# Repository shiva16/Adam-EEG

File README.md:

# Adam-EEG

**India's first open-hardware 32-channel EEG / biopotential acquisition board** — a quad-ADS1299 analog front end driven by a dual-ATmega328 controller, designed in EAGLE by [Soul Scientific](https://github.com/shiva16) in 2015.

Adam-EEG packs four Texas Instruments **ADS1299** 24-bit, 8-channel simultaneous-sampling analog front ends onto one board — 32 truly simultaneous EEG channels, daisy-chained over a single SPI bus — with onboard microSD logging for fully standalone (untethered) recording. It's the original prototype in the Adam-EEG lineage: a from-scratch, low-cost, open alternative to research-grade EEG acquisition hardware.

**Also published at:** [Hackaday.io](https://hackaday.io/project/206308-adam-eeg-open-source-32-channel-eeg-board) · [dev.to](https://dev.to/shiva16/adam-eeg-an-open-source-32-channel-eeg-board-from-2015-quad-ads1299-dual-atmega328-2gfi) · [NeuroTechX/awesome-bci](https://github.com/NeuroTechX/awesome-bci#consumer-and-diy-devices) ([merged](https://github.com/NeuroTechX/awesome-bci/pull/92))

---

## Table of contents

- [Why this exists](#why-this-exists)
- [Technical specifications](#technical-specifications)
- [Connectors & pinout](#connectors--pinout)
- [Passive component reference](#passive-component-reference)
- [System architecture](#system-architecture)
- [Repository contents](#repository-contents)
- [Getting started](#getting-started)
- [Safety & disclaimer](#safety--disclaimer)
- [Roadmap](#roadmap)
- [Contributing](#contributing)
- [License](#license)

---

## Why this exists

Research-grade multichannel EEG hardware is expensive and closed. Adam-EEG set out to prove that a **32-channel, simultaneous-sampling, standalone-logging** EEG acquisition board could be built from commodity parts, in a hobbyist CAD tool, at a fraction of the cost — fully open, so anyone can build on it rather than starting from a datasheet.

## Technical specifications

| Subsystem | Detail |
|---|---|
| **Analog front end** | 4 × Texas Instruments **ADS1299** — 24-bit, 8-channel, simultaneous-sampling, low-noise biopotential ADC |
| **Total channels** | **32** unipolar channels + common reference, fully simultaneous (no muxing) |
| **AFE interconnect** | Multi-device SPI **daisy-chain** — shared `SCLK`/`DIN`/`DOUT`/`DRDY`, individual `CS1`–`CS4` per ADS1299 |
| **Controller** | 2 × **ATmega328** (SMD, Arduino-compatible core) |
| **Programming** | 2 × 6-pin AVR ISP headers |
| **Onboard storage** | microSD socket — standalone data logging, no host PC required |
| **Power** | Onboard bipolar analog rail generation: LM2663 switched-capacitor inverter + LP5907 / TPS723xx LDOs for clean split supplies to the AFEs |
| **Clocking** | 2 × crystal oscillators |
| **I/O** | 6 × 1×2, 3 × 1×8, 1 × 1×11, 1 × 1×18 pin headers (electrode + expansion) |
| **Board** | 2-layer, **97.2 × 81.9 mm** (~79.6 cm²), 2 × Ø3.2 mm mounting holes |
| **Complexity** | 354 schematic parts / 229 placed board elements |
| **CAD format** | EAGLE 6.6.0 XML (`.sch` / `.brd`) — single schematic sheet |
| **License** | Apache License 2.0 |

## Connectors & pinout

Extracted directly from the schematic's named nets — real signal names, not inferred from silkscreen alone.

| Connector | Type | Signals | Role |
|---|---|---|---|
| `ARDUINO_CONN` | 1×11 header | `CS1`–`CS4`, `SCLK`, `DIN`, `DOUT`, `DRDY`, `RST`, `PD`, `STRT` | Full SPI daisy-chain + control breakout — lets an external Arduino-compatible host drive all 4 ADS1299 directly, independent of the onboard ATmega328s |
| `ELECTRODES_P&N` | 1×18 header | 18 electrode nets | Primary differential (P/N) electrode input header |
| `ELECTRODES` / `ELECTRODES1` / `ELECTRODES2` | 3× 1×8 header | Per-channel buffered outputs (`1O1`–`8O1`, `1O2`–`8O2`, `1O3`–`8O3`) | Buffered channel-output test/tap points for 3 of the 4 ADS1299s |
| `POWER_PIN` | 1×2 header | `+5V`, `AGND` | Main board power input, feeding the onboard LDO/charge-pump regulation |
| `JP3`–`JP5` | 1×2 jumpers | `DIN`/`JU1`, `DOUT`/`JU2`, `SCLK`/`JU3` | In-line jumpers on the SPI data/clock lines (break/test-point access) |
| `JP1`–`JP2` | 1×2 jumpers | Internal (unlabeled) nets | Present in the schematic; exact function isn't silkscreen-documented — trace before relying on them |

## Passive component reference

Most-used passive values, pulled from the real `value=` attributes in the schematic (useful for a BOM sanity-check or respin):

| Component class | Dominant value | Count | Likely role |
|---|---|---|---|
| Resistor | 5 kΩ | 60 of 69 | Per-channel bias/lead-off network (matches ADS1299's typical RLD topology) |
| Capacitor | 4.7 nF | 48 of 127 | Per-channel input RC filtering |
| Capacitor | 1 µF | 36 of 127 | Local/bulk decoupling |
| Capacitor | 0.1 µF | 28 of 127 | High-frequency decoupling |
| Capacitor | 10 µF / 100 µF | 7 / 4 | Bulk supply-rail reservoirs |
| Crystal | 32.768 kHz (`Y1` or `Y2`, confirmed in schematic text) | 1 of 2 | Real-time/watchdog clock — the second crystal has no frequency called out in the schematic text, verify before assuming a value |

## System architecture

```mermaid
flowchart LR
    subgraph AFE["Analog Front End"]
        A1["ADS1299 #1<br/>ch 1-8"]
        A2["ADS1299 #2<br/>ch 9-16"]
        A3["ADS1299 #3<br/>ch 17-24"]
        A4["ADS1299 #4<br/>ch 25-32"]
    end
    A1 -- "DOUT daisy" --> A2 -- "DOUT daisy" --> A3 -- "DOUT daisy" --> A4
    MCU["Dual ATmega328<br/>controller"]
    A1 <-- "shared SCLK / DIN / DRDY<br/>individual CS1-CS4" --> MCU
    A2 <-.-> MCU
    A3 <-.-> MCU
    A4 <-.-> MCU
    MCU --> SD["microSD<br/>standalone logging"]
    PWR["LM2663 charge pump<br/>+ LP5907 / TPS723xx LDOs"] --> AFE
    ISP["2x AVR ISP header"] --> MCU
```

Each ADS1299 samples 8 channels simultaneously; the four devices share one SPI bus in TI's standard multi-device daisy-chain topology, so all 32 channels are read out in lockstep with no channel-to-channel skew.

## Repository contents

| Path | Description |
|---|---|
| `EEG_64_1.zip` | Full EAGLE source — `EEG_64.sch` (schematic) + `EEG_64_1.brd` (board layout) |
| `LICENSE` | Apache License 2.0 |
| `CONTRIBUTING.md` | How to propose changes, report issues, or contribute a fabricated/tested revision |
| `CODE_OF_CONDUCT.md` | Community standards for this repository |
| `.github/` | Issue and pull request templates |

## Getting started

1. Install [Autodesk EAGLE](https://www.autodesk.com/products/eagle/overview) (a free tier is sufficient — this board's ≤80 cm², 2-layer, single-sheet design was scoped to fit within EAGLE's classic free-tier limits).
2. Clone this repo and unzip `EEG_64_1.zip`.
3. Open `EEG_64.sch` for the schematic or `EEG_64_1.brd` for the board layout — both are standard EAGLE XML and can also be inspected with `eagle2kicad`-style converters if you prefer KiCad.
4. Gerbers are not checked in — export them from the `.brd` via EAGLE's CAM processor if you're sending this to fab.

## Safety & disclaimer

This is an **open-hardware research/prototyping board**, not a certified medical device. It has not undergone FDA/CE or equivalent regulatory clearance, and no formal patient-isolation or leakage-current certification has been performed on this design. If you build and use this board:

- Do **not** use it for clinical diagnosis or treatment decisions.
- Power it only from isolated, battery-backed supplies — never connect a build to mains-powered equipment while it is attached to a person.
- Treat it as you would any DIY biopotential-acquisition project: informed use, at your own risk.

## Roadmap

This 2015 quad-ADS1299 board is the original Adam-EEG prototype. It remains a solid, low-cost 32-channel reference design for anyone building EEG/BCI acquisition hardware from scratch. Later Adam-EEG iterations explore denser single-chip AFE options; this repository stays focused on the original, fully-verified quad-ADS1299 design.

## Contributing

Issues and pull requests are welcome — see [CONTRIBUTING.md](CONTRIBUTING.md). Whether it's a routing improvement, a KiCad conversion, a BOM/sourcing update, or a build log from your own fab run, please open an issue first so we can track it.

## License

Apache License 2.0 — see [LICENSE](LICENSE). You are free to use, modify, and distribute this design, including commercially, provided attribution is preserved.

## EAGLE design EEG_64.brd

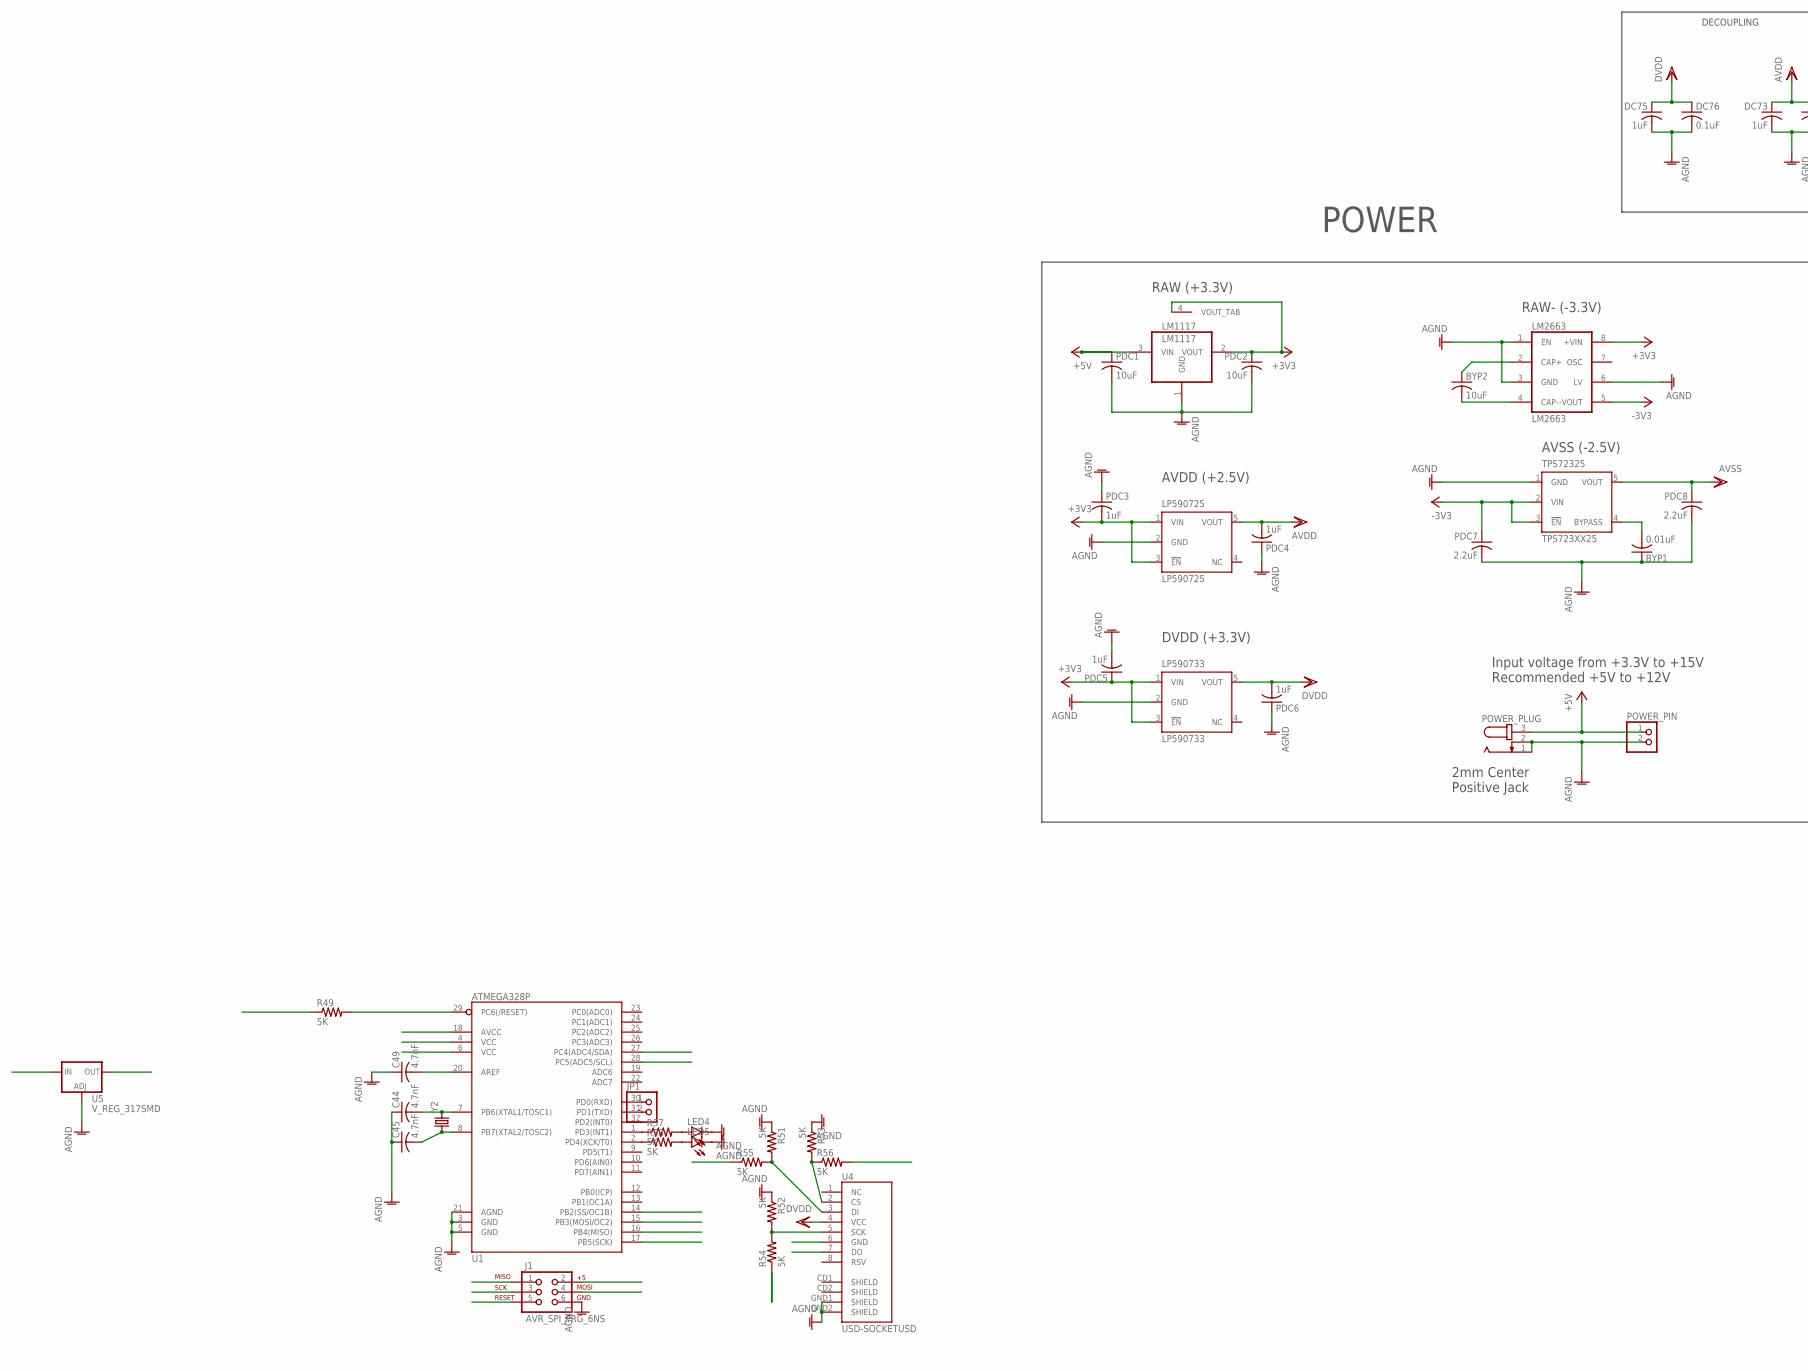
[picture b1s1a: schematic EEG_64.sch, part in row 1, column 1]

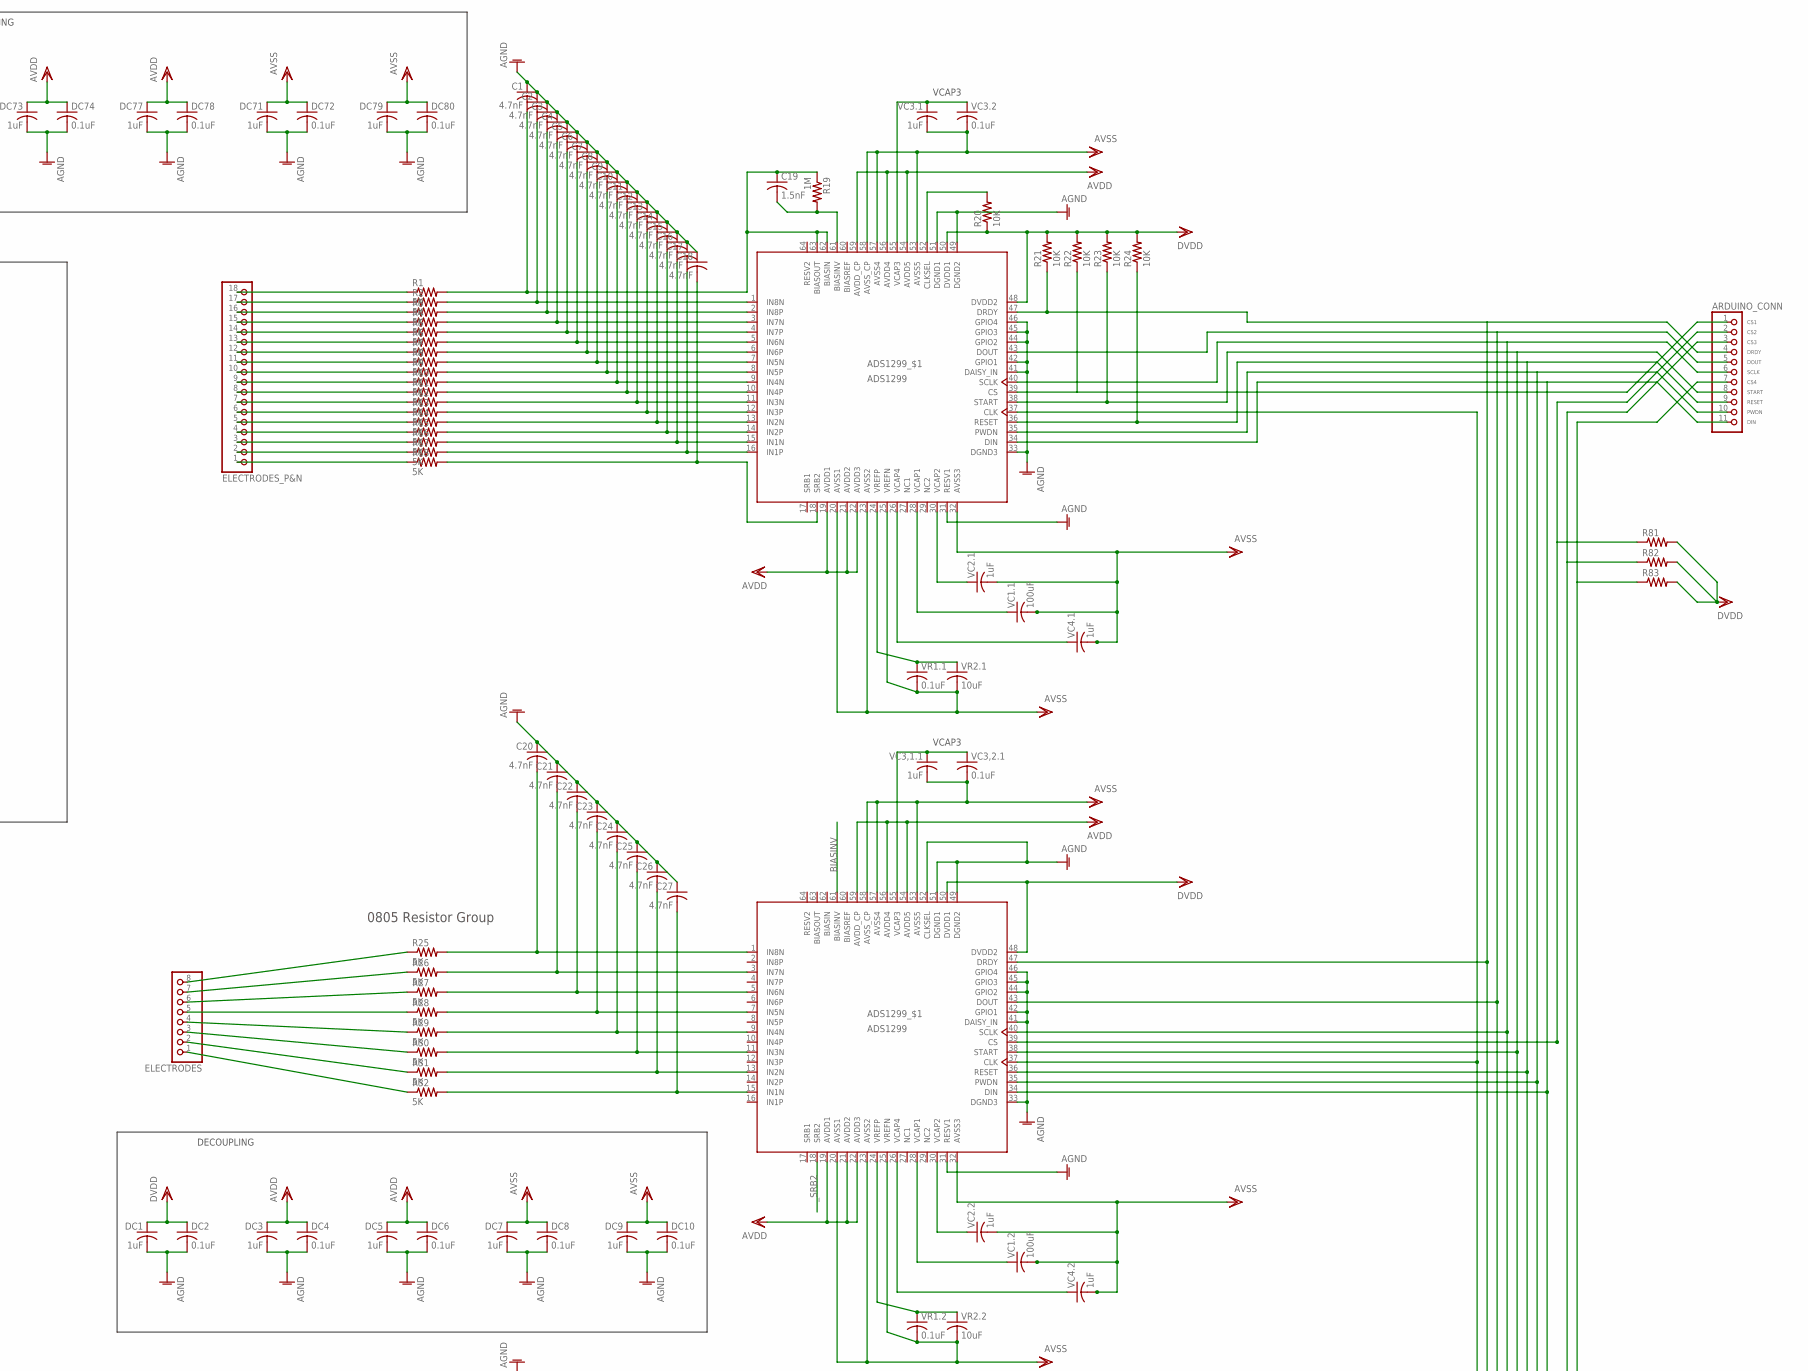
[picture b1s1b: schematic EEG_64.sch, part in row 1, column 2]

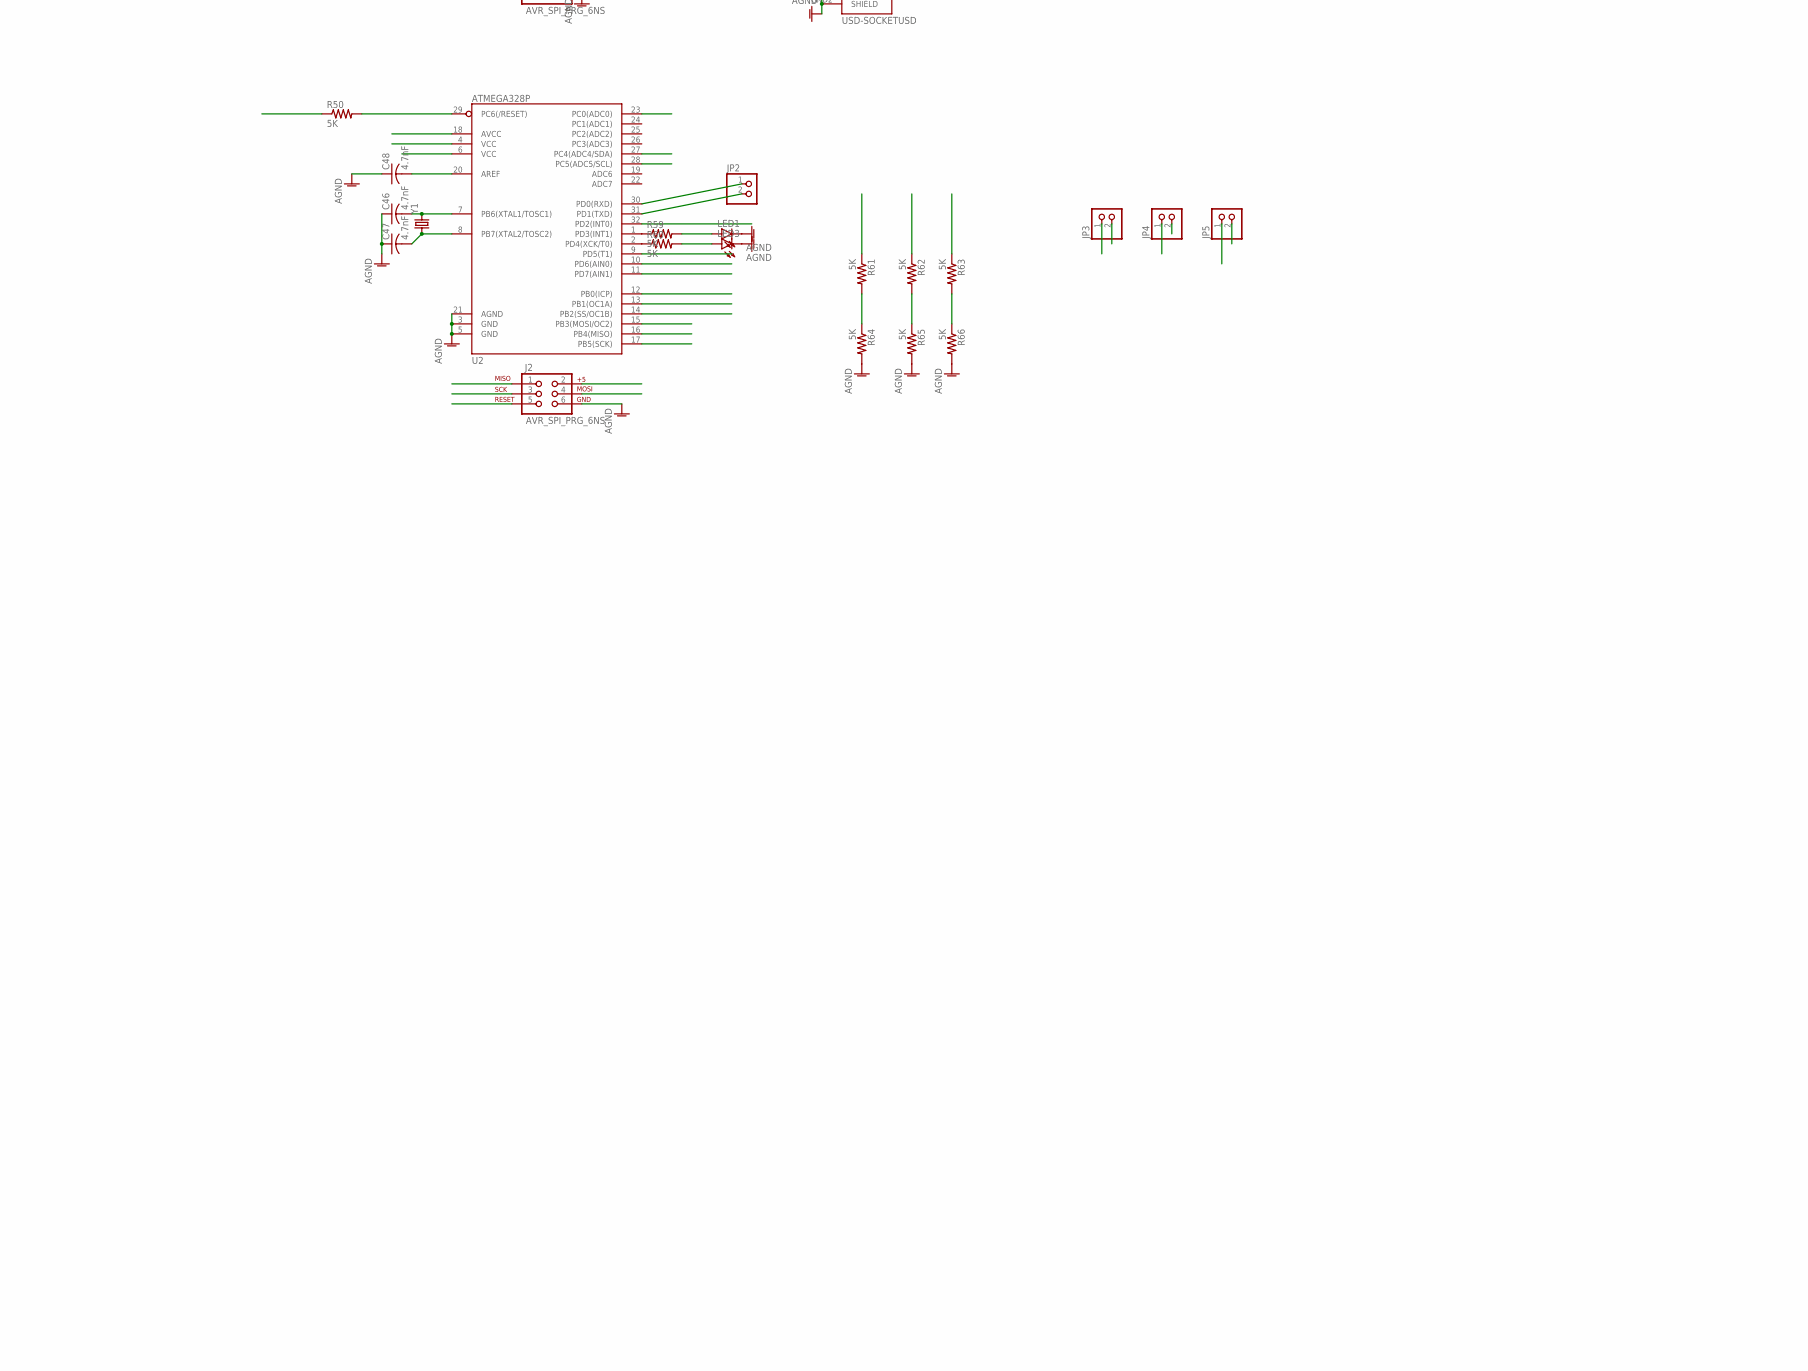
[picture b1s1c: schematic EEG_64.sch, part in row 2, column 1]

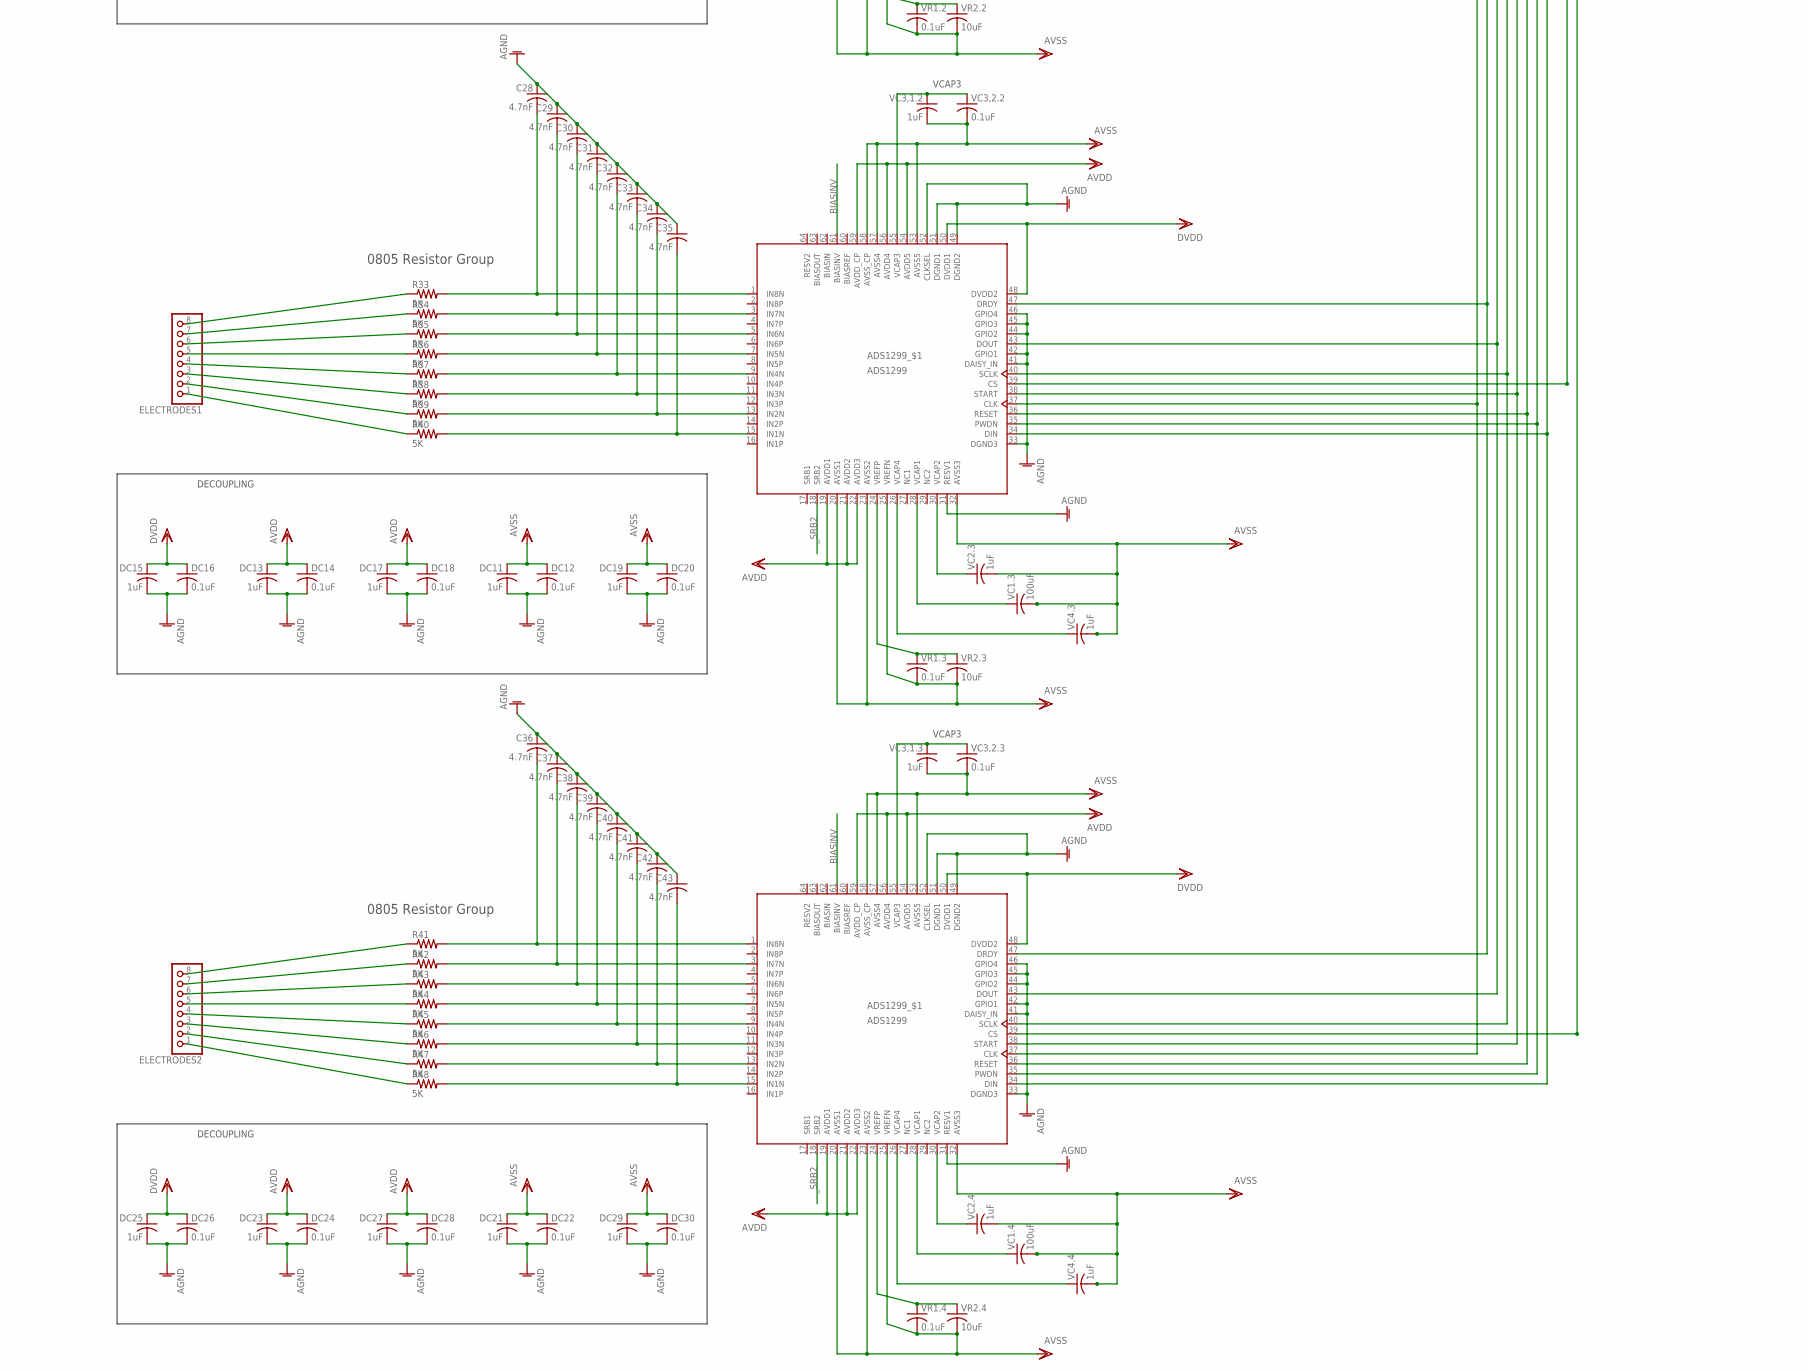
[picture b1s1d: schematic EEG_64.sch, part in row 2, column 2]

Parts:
ADS1, ADS2, ADS3, ADS4: ADS1299; PAG_S-PQFP-G64
ARDUINO_CONN: PINHD-1X11; 1X11
BYP1: 0.01uF; C0603
BYP2: 10uF; C0603
C1, C2, C3, C4, C5, C6, C7, C8, C9, C10, C11, C12, C13, C14, C15, C16, C17, C18, C20, C21, C22, C23, C24, C25, C26, C27, C28, C29, C30, C31, C32, C33, C34, C35, C36, C37, C38, C39, C40, C41, C42, C43, C44, C45, C46, C47, C48, C49: 4.7nF; C0603
C19: 1.5nF; C0603
DC1, DC3, DC5, DC7, DC9, DC11, DC13, DC15, DC17, DC19, DC21, DC23, DC25, DC27, DC29, DC71, DC73, DC75, DC77, DC79: 1uF; C0603
DC2, DC4, DC6, DC8, DC10, DC12, DC14, DC16, DC18, DC20, DC22, DC24, DC26, DC28, DC30, DC72, DC74, DC76, DC78, DC80: 0.1uF; C0603
ELECTRODES, ELECTRODES1, ELECTRODES2: PINHD-1X8; 1X08
ELECTRODES_P&N: PINHD-1X18; 1X18
J1, J2: AVR_SPI_PRG_6NS; 2X3-NS
JP1, JP2, JP3, JP4, JP5: PINHD-1X2; 1X02
LED1, LED3, LED4, LED5: LED0603; LED-0603
LM1117: LM1117; SOT223
LM2663: LM2663; SO-08
LP590725: LP590725; SOT23-DBV
LP590733: LP590733; SOT23-DBV
PDC1, PDC2: 10uF; C0603
PDC3, PDC4, PDC5, PDC6: 1uF; C0603
PDC7, PDC8: 2.2uF; C0603
POWER_PIN: PINHD-1X2; 1X02
POWER_PLUG: JACK-PLUG0; SPC4077
R1, R2, R3, R4, R5, R6, R7, R8, R9, R10, R11, R12, R13, R14, R15, R16, R17, R18, R25, R26, R27, R28, R29, R30, R31, R32, R33, R34, R35, R36, R37, R38, R39, R40, R41, R42, R43, R44, R45, R46, R47, R48, R49, R50, R51, R52, R53, R54, R55, R56, R57, R58, R59, R60, R61, R62, R63, R64, R65, R66: 5K; R0603
R19: 1M; R0603
R20, R21, R22, R23, R24: 10K; R0603
R81, R82, R83: R-US_R0603; R0603
TPS72325: TPS723XX25; SOT23-DBV
U1, U2: ATMEGA328P; TQFP32-08
U4: USD-SOCKETUSD; USD-SOCKET-PP
U5: V_REG_317SMD; SOT223
VC1.1, VC1.2, VC1.3, VC1.4: 100uF; C0603
VC2.1, VC2.2, VC2.3, VC2.4, VC3,1.1, VC3,1.2, VC3,1.3, VC3.1, VC4.1, VC4.2, VC4.3, VC4.4: 1uF; C0603
VC3,2.1, VC3,2.2, VC3,2.3, VC3.2: 0.1uF; C0603
VR1.1, VR1.2, VR1.3, VR1.4: 0.1uF; C0603
VR2.1, VR2.2, VR2.3, VR2.4: 10uF; C0603
Y1, Y2: CRYSTAL5X3; CRYSTAL-SMD-5X3

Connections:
+3V3: LM1117.2 (VOUT), LM1117.4 (VOUT_TAB), LM2663.8 (+VIN), LP590725.1 (VIN), LP590725.3 (!EN), LP590733.1 (VIN), LP590733.3 (!EN), PDC2.1, PDC3.2, PDC5.1
+5V: LM1117.3 (VIN), PDC1.1, POWER_PIN.1, POWER_PLUG.3, U5.3 (IN)
-3V3: LM2663.5 (-VOUT), PDC7.1, TPS72325.2 (VIN), TPS72325.3 (!EN)
AGND: ADS1.31 (RESV1), ADS1.33 (DGND3), ADS1.41 (DAISY_IN), ADS1.42 (GPIO1), ADS1.44 (GPIO2), ADS1.45 (GPIO3), ADS1.46 (GPIO4), ADS1.49 (DGND2), ADS1.51 (DGND1), ADS2.31 (RESV1), ADS2.33 (DGND3), ADS2.41 (DAISY_IN), ADS2.42 (GPIO1), ADS2.44 (GPIO2), ADS2.45 (GPIO3), ADS2.46 (GPIO4), ADS2.49 (DGND2), ADS2.51 (DGND1), ADS2.52 (CLKSEL), ADS3.31 (RESV1), ADS3.33 (DGND3), ADS3.41 (DAISY_IN), ADS3.42 (GPIO1), ADS3.44 (GPIO2), ADS3.45 (GPIO3), ADS3.46 (GPIO4), ADS3.49 (DGND2), ADS3.51 (DGND1), ADS3.52 (CLKSEL), ADS4.31 (RESV1), ADS4.33 (DGND3), ADS4.41 (DAISY_IN), ADS4.42 (GPIO1), ADS4.44 (GPIO2), ADS4.45 (GPIO3), ADS4.46 (GPIO4), ADS4.49 (DGND2), ADS4.51 (DGND1), ADS4.52 (CLKSEL), BYP1.1, C1.1, C2.1, C3.1, C4.1, C5.1, C6.1, C7.1, C8.1, C9.1, C10.1, C11.1, C12.1, C13.1, C14.1, C15.1, C16.1, C17.1, C18.1, C20.1, C21.1, C22.1, C23.1, C24.1, C25.1, C26.1, C27.1, C28.1, C29.1, C30.1, C31.1, C32.1, C33.1, C34.1, C35.1, C36.1, C37.1, C38.1, C39.1, C40.1, C41.1, C42.1, C43.1, C44.1, C45.1, C46.1, C47.1, C48.1, C49.1, DC1.2, DC2.2, DC3.2, DC4.2, DC5.2, DC6.2, DC7.2, DC8.2, DC9.2, DC10.2, DC11.2, DC12.2, DC13.2, DC14.2, DC15.2, DC16.2, DC17.2, DC18.2, DC19.2, DC20.2, DC21.2, DC22.2, DC23.2, DC24.2, DC25.2, DC26.2, DC27.2, DC28.2, DC29.2, DC30.2, DC71.2, DC72.2, DC73.2, DC74.2, DC75.2, DC76.2, DC77.2, DC78.2, DC79.2, DC80.2, J1.6, J2.6, LED1.C, LED3.C, LED4.C, LED5.C, LM1117.1 (GND), LM2663.1 (EN), LM2663.3 (GND), LM2663.6 (LV), LP590725.2 (GND), LP590733.2 (GND), PDC1.2, PDC2.2, PDC3.1, PDC4.1, PDC5.2, PDC6.1, PDC7.2, PDC8.2, POWER_PIN.2, POWER_PLUG.1, POWER_PLUG.2, R51.1, R52.1, R53.1, R64.2, R65.2, R66.2, TPS72325.1 (GND), U1.3 (GND), U1.5 (GND), U1.21 (AGND), U2.3 (GND), U2.5 (GND), U2.21 (AGND), U4.GND1 (SHIELD), U4.GND2 (SHIELD), U5.1 (ADJ)
AVDD: ADS1.19 (AVDD1), ADS1.21 (AVDD2), ADS1.22 (AVDD3), ADS1.54 (AVDD5), ADS1.56 (AVDD4), ADS1.59 (AVDD_CP), ADS2.19 (AVDD1), ADS2.21 (AVDD2), ADS2.22 (AVDD3), ADS2.54 (AVDD5), ADS2.56 (AVDD4), ADS2.59 (AVDD_CP), ADS3.19 (AVDD1), ADS3.21 (AVDD2), ADS3.22 (AVDD3), ADS3.54 (AVDD5), ADS3.56 (AVDD4), ADS3.59 (AVDD_CP), ADS4.19 (AVDD1), ADS4.21 (AVDD2), ADS4.22 (AVDD3), ADS4.54 (AVDD5), ADS4.56 (AVDD4), ADS4.59 (AVDD_CP), DC3.1, DC4.1, DC5.1, DC6.1, DC13.1, DC14.1, DC17.1, DC18.1, DC23.1, DC24.1, DC27.1, DC28.1, DC73.1, DC74.1, DC77.1, DC78.1, LP590725.5 (VOUT), PDC4.2
AVSS: ADS1.20 (AVSS1), ADS1.23 (AVSS2), ADS1.25 (VREFN), ADS1.32 (AVSS3), ADS1.53 (AVSS5), ADS1.57 (AVSS4), ADS1.58 (AVSS_CP), ADS2.20 (AVSS1), ADS2.23 (AVSS2), ADS2.25 (VREFN), ADS2.32 (AVSS3), ADS2.53 (AVSS5), ADS2.57 (AVSS4), ADS2.58 (AVSS_CP), ADS3.20 (AVSS1), ADS3.23 (AVSS2), ADS3.25 (VREFN), ADS3.32 (AVSS3), ADS3.53 (AVSS5), ADS3.57 (AVSS4), ADS3.58 (AVSS_CP), ADS4.20 (AVSS1), ADS4.23 (AVSS2), ADS4.25 (VREFN), ADS4.32 (AVSS3), ADS4.53 (AVSS5), ADS4.57 (AVSS4), ADS4.58 (AVSS_CP), DC7.1, DC8.1, DC9.1, DC10.1, DC11.1, DC12.1, DC19.1, DC20.1, DC21.1, DC22.1, DC29.1, DC30.1, DC71.1, DC72.1, DC79.1, DC80.1, PDC8.1, TPS72325.5 (VOUT), VC1.1.2, VC1.2.2, VC1.3.2, VC1.4.2, VC2.1.2, VC2.2.2, VC2.3.2, VC2.4.2, VC3,1.1.2, VC3,1.2.2, VC3,1.3.2, VC3,2.1.2, VC3,2.2.2, VC3,2.3.2, VC3.1.2, VC3.2.2, VC4.1.2, VC4.2.2, VC4.3.2, VC4.4.2, VR1.1.2, VR1.2.2, VR1.3.2, VR1.4.2, VR2.1.2, VR2.2.2, VR2.3.2, VR2.4.2
BIASINV: ADS1.61 (BIASINV), ADS2.61 (BIASINV), ADS3.61 (BIASINV), ADS4.61 (BIASINV), C19.2, R19.2
CLK: U1.28 (PC5(ADC5/SCL)), U2.28 (PC5(ADC5/SCL))
CS: R56.2, U1.14 (PB2(SS/OC1B))
DVDD: ADS1.48 (DVDD2), ADS1.50 (DVDD1), ADS2.48 (DVDD2), ADS2.50 (DVDD1), ADS3.48 (DVDD2), ADS3.50 (DVDD1), ADS4.48 (DVDD2), ADS4.50 (DVDD1), DC1.1, DC2.1, DC15.1, DC16.1, DC25.1, DC26.1, DC75.1, DC76.1, LP590733.5 (VOUT), PDC6.2, R20.1, R21.2, R22.2, R23.2, R24.2, R81.2, R82.2, R83.2, U4.4 (VCC)
JU1: JP3.1, R61.2, R64.1
JU2: JP4.1, R62.2, R65.1
JU3: JP5.1, R63.2, R66.1
MISO1: J1.1, U1.16 (PB4(MISO)), U4.7 (DO)
MISO2: J2.1, R62.1, U2.16 (PB4(MISO))
MOSI1: J1.4, R55.1, U1.15 (PB3(MOSI/OC2))
MOSI2: J2.4, R61.1, U2.15 (PB3(MOSI/OC2))
unnamed: ADS1.62 (BIASIN), ADS1.63 (BIASOUT), C1.2, C19.1, R1.2, R19.1
unnamed: JP1.1, U1.30 (PD0(RXD))
unnamed: ADS1.2 (IN8P), C3.2, R3.2
unnamed: ADS1.55 (VCAP3), VC3.1.1, VC3.2.1
unnamed: ADS1.3 (IN7N), C4.2, R4.2
unnamed: ADS1.1 (IN8N), C2.2, R2.2
unnamed: ADS1.4 (IN7P), C5.2, R5.2
unnamed: ADS1.5 (IN6N), C6.2, R6.2
unnamed: ADS1.6 (IN6P), C7.2, R7.2
unnamed: ADS1.7 (IN5N), C8.2, R8.2
unnamed: ADS1.8 (IN5P), C9.2, R9.2
unnamed: ADS1.9 (IN4N), C10.2, R10.2
unnamed: ADS1.10 (IN4P), C11.2, R11.2
unnamed: ADS1.11 (IN3N), C12.2, R12.2
unnamed: ADS1.12 (IN3P), C13.2, R13.2
unnamed: ADS1.13 (IN2N), C14.2, R14.2
unnamed: ADS1.14 (IN2P), C15.2, R15.2
unnamed: ADS1.15 (IN1N), C16.2, R16.2
unnamed: ADS1.16 (IN1P), C17.2, R17.2
unnamed: C44.2, U1.7 (PB6(XTAL1/TOSC1)), Y2.3 (2)
unnamed: C45.2, U1.8 (PB7(XTAL2/TOSC2)), Y2.1
unnamed: C46.2, U2.7 (PB6(XTAL1/TOSC1)), Y1.3 (2)
unnamed: C47.2, U2.8 (PB7(XTAL2/TOSC2)), Y1.1
unnamed: C48.2, U2.20 (AREF)
unnamed: ADS1.52 (CLKSEL), R20.2
unnamed: ADS1.24 (VREFP), VR1.1.1, VR2.1.1
unnamed: ADS1.26 (VCAP4), VC4.1.1
unnamed: ADS1.28 (VCAP1), VC1.1.1
unnamed: ADS1.30 (VCAP2), VC2.1.1
unnamed: BYP1.2, TPS72325.4 (BYPASS)
unnamed: BYP2.1, LM2663.2 (CAP+)
unnamed: BYP2.2, LM2663.4 (CAP-)
unnamed: ELECTRODES_P&N.18, R1.1
unnamed: ELECTRODES_P&N.17, R2.1
unnamed: ELECTRODES_P&N.16, R3.1
unnamed: ELECTRODES_P&N.15, R4.1
unnamed: ELECTRODES_P&N.14, R5.1
unnamed: ELECTRODES_P&N.13, R6.1
unnamed: ELECTRODES_P&N.12, R7.1
unnamed: ELECTRODES_P&N.11, R8.1
unnamed: ELECTRODES_P&N.10, R9.1
unnamed: ELECTRODES_P&N.9, R10.1
unnamed: ELECTRODES_P&N.8, R11.1
unnamed: ELECTRODES_P&N.7, R12.1
unnamed: ELECTRODES_P&N.6, R13.1
unnamed: ELECTRODES_P&N.5, R14.1
unnamed: ELECTRODES_P&N.4, R15.1
unnamed: ELECTRODES_P&N.3, R16.1
unnamed: ELECTRODES_P&N.2, R17.1
unnamed: ELECTRODES_P&N.1, R18.1
unnamed: C49.2, U1.20 (AREF)
unnamed: R51.2, R55.2, U4.3 (DI)
unnamed: R52.2, R54.2, U4.5 (SCK)
unnamed: R53.2, R56.1, U4.2 (CS)
unnamed: JP1.2, U1.31 (PD1(TXD))
unnamed: JP2.1, U2.30 (PD0(RXD))
unnamed: JP2.2, U2.31 (PD1(TXD))
unnamed: R57.1, U1.1 (PD3(INT1))
unnamed: R58.1, U1.2 (PD4(XCK/T0))
unnamed: R59.1, U2.1 (PD3(INT1))
unnamed: R60.1, U2.2 (PD4(XCK/T0))
unnamed: LED1.A, R59.2
unnamed: LED3.A, R60.2
unnamed: LED4.A, R57.2
unnamed: LED5.A, R58.2
OUT: J1.2, J2.2, R49.1, R50.1, U1.4 (VCC), U1.6 (VCC), U1.18 (AVCC), U2.4 (VCC), U2.6 (VCC), U2.18 (AVCC), U5.2 (OUT)
RST1: J1.5, R49.2, U1.29 (PC6(/RESET))
RST2: J2.5, R50.2, U2.29 (PC6(/RESET))
SCK1: J1.3, R54.1, U1.17 (PB5(SCK))
SCK2: J2.3, R63.1, U2.17 (PB5(SCK))
SDA: U1.27 (PC4(ADC4/SDA)), U2.27 (PC4(ADC4/SDA))
_1IN1: ADS2.15 (IN1N), C27.2, R32.2
_1IN2: ADS3.15 (IN1N), C35.2, R40.2
_1IN3: ADS4.15 (IN1N), C43.2, R48.2
_1O1: ELECTRODES.1, R32.1
_1O2: ELECTRODES1.1, R40.1
_1O3: ELECTRODES2.1, R48.1
_2IN1: ADS2.13 (IN2N), C26.2, R31.2
_2IN2: ADS3.13 (IN2N), C34.2, R39.2
_2IN3: ADS4.13 (IN2N), C42.2, R47.2
_2O1: ELECTRODES.2, R31.1
_2O2: ELECTRODES1.2, R39.1
_2O3: ELECTRODES2.2, R47.1
_3IN1: ADS2.11 (IN3N), C25.2, R30.2
_3IN2: ADS3.11 (IN3N), C33.2, R38.2
_3IN3: ADS4.11 (IN3N), C41.2, R46.2
_3O1: ELECTRODES.3, R30.1
_3O2: ELECTRODES1.3, R38.1
_3O3: ELECTRODES2.3, R46.1
_4IN1: ADS2.9 (IN4N), C24.2, R29.2
_4IN2: ADS3.9 (IN4N), C32.2, R37.2
_4IN3: ADS4.9 (IN4N), C40.2, R45.2
_4O1: ELECTRODES.4, R29.1
_4O2: ELECTRODES1.4, R37.1
_4O3: ELECTRODES2.4, R45.1
_5IN1: ADS2.7 (IN5N), C23.2, R28.2
_5IN2: ADS3.7 (IN5N), C31.2, R36.2
_5IN3: ADS4.7 (IN5N), C39.2, R44.2
_5O1: ELECTRODES.5, R28.1
_5O2: ELECTRODES1.5, R36.1
_5O3: ELECTRODES2.5, R44.1
_6IN1: ADS2.5 (IN6N), C22.2, R27.2
_6IN2: ADS3.5 (IN6N), C30.2, R35.2
_6IN3: ADS4.5 (IN6N), C38.2, R43.2
_6O1: ELECTRODES1.6, R35.1
_6O2: ELECTRODES.6, R27.1
_6O3: ELECTRODES2.6, R43.1
_7IN1: ADS2.3 (IN7N), C21.2, R26.2
_7IN2: ADS3.3 (IN7N), C29.2, R34.2
_7IN3: ADS4.3 (IN7N), C37.2, R42.2
_7O1: ELECTRODES.7, R26.1
_7O2: ELECTRODES1.7, R34.1
_7O3: ELECTRODES2.7, R42.1
_8IN1: ADS2.1 (IN8N), C20.2, R25.2
_8IN2: ADS3.1 (IN8N), C28.2, R33.2
_8IN3: ADS4.1 (IN8N), C36.2, R41.2
_8O1: ELECTRODES.8, R25.1
_8O2: ELECTRODES1.8, R33.1
_8O3: ELECTRODES2.8, R41.1
_CLK: ADS1.37 (CLK), ADS2.37 (CLK), ADS3.37 (CLK), ADS4.37 (CLK)
_CS1: ADS1.39 (CS), ARDUINO_CONN.1, R22.1, U2.11 (PD7(AIN1))
_CS2: ADS2.39 (CS), ARDUINO_CONN.2, R81.1, U2.12 (PB0(ICP))
_CS3: ADS3.39 (CS), ARDUINO_CONN.3, R82.1, U2.13 (PB1(OC1A))
_CS4: ADS4.39 (CS), ARDUINO_CONN.7, R83.1, U2.14 (PB2(SS/OC1B))
_DIN: ADS1.34 (DIN), ADS2.34 (DIN), ADS3.34 (DIN), ADS4.34 (DIN), ARDUINO_CONN.11, JP3.2
_DOUT: ADS1.43 (DOUT), ADS2.43 (DOUT), ADS3.43 (DOUT), ADS4.43 (DOUT), ARDUINO_CONN.5, JP4.2
_DRDY: ADS1.47 (DRDY), ADS2.47 (DRDY), ADS3.47 (DRDY), ADS4.47 (DRDY), ARDUINO_CONN.4, R21.1, U2.10 (PD6(AIN0))
_PD: ADS1.35 (PWDN), ADS2.35 (PWDN), ADS3.35 (PWDN), ADS4.35 (PWDN), ARDUINO_CONN.10, U2.23 (PC0(ADC0))
_RST: ADS1.36 (RESET), ADS2.36 (RESET), ADS3.36 (RESET), ADS4.36 (RESET), ARDUINO_CONN.9, R24.1, U2.32 (PD2(INT0))
_SCLK: ADS1.40 (SCLK), ADS2.40 (SCLK), ADS3.40 (SCLK), ADS4.40 (SCLK), ARDUINO_CONN.6, JP5.2
_SRB2: ADS1.18 (SRB2), ADS2.18 (SRB2), ADS3.18 (SRB2), ADS4.18 (SRB2), C18.2, R18.2
_STRT: ADS1.38 (START), ADS2.38 (START), ADS3.38 (START), ADS4.38 (START), ARDUINO_CONN.8, R23.1, U2.9 (PD5(T1))
_VC1.1: ADS2.28 (VCAP1), VC1.2.1
_VC1.2: ADS3.28 (VCAP1), VC1.3.1
_VC1.3: ADS4.28 (VCAP1), VC1.4.1
_VC2.1: ADS2.30 (VCAP2), VC2.2.1
_VC2.2: ADS3.30 (VCAP2), VC2.3.1
_VC2.3: ADS4.30 (VCAP2), VC2.4.1
_VC3.1: ADS2.55 (VCAP3), VC3,1.1.1, VC3,2.1.1
_VC3.2: ADS3.55 (VCAP3), VC3,1.2.1, VC3,2.2.1
_VC3.3: ADS4.55 (VCAP3), VC3,1.3.1, VC3,2.3.1
_VC4.1: ADS2.26 (VCAP4), VC4.2.1
_VC4.2: ADS3.26 (VCAP4), VC4.3.1
_VC4.3: ADS4.26 (VCAP4), VC4.4.1
_VRP1: ADS2.24 (VREFP), VR1.2.1, VR2.2.1
_VRP2: ADS3.24 (VREFP), VR1.3.1, VR2.3.1
_VRP3: ADS4.24 (VREFP), VR1.4.1, VR2.4.1

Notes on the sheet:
VCAP3
SCLK
PWDN
RESET
START
DRDY
DOUT
DIN
CS1
CS2
CS3
POWER
DVDD (+3.3V)
AVDD (+2.5V)
AVSS (-2.5V)
RAW (+3.3V)
RAW- (-3.3V)
2mm Center Positive Jack
Input voltage from +3.3V to +15V Recommended +5V to +12V
CS4
0805 Resistor Group
DECOUPLING

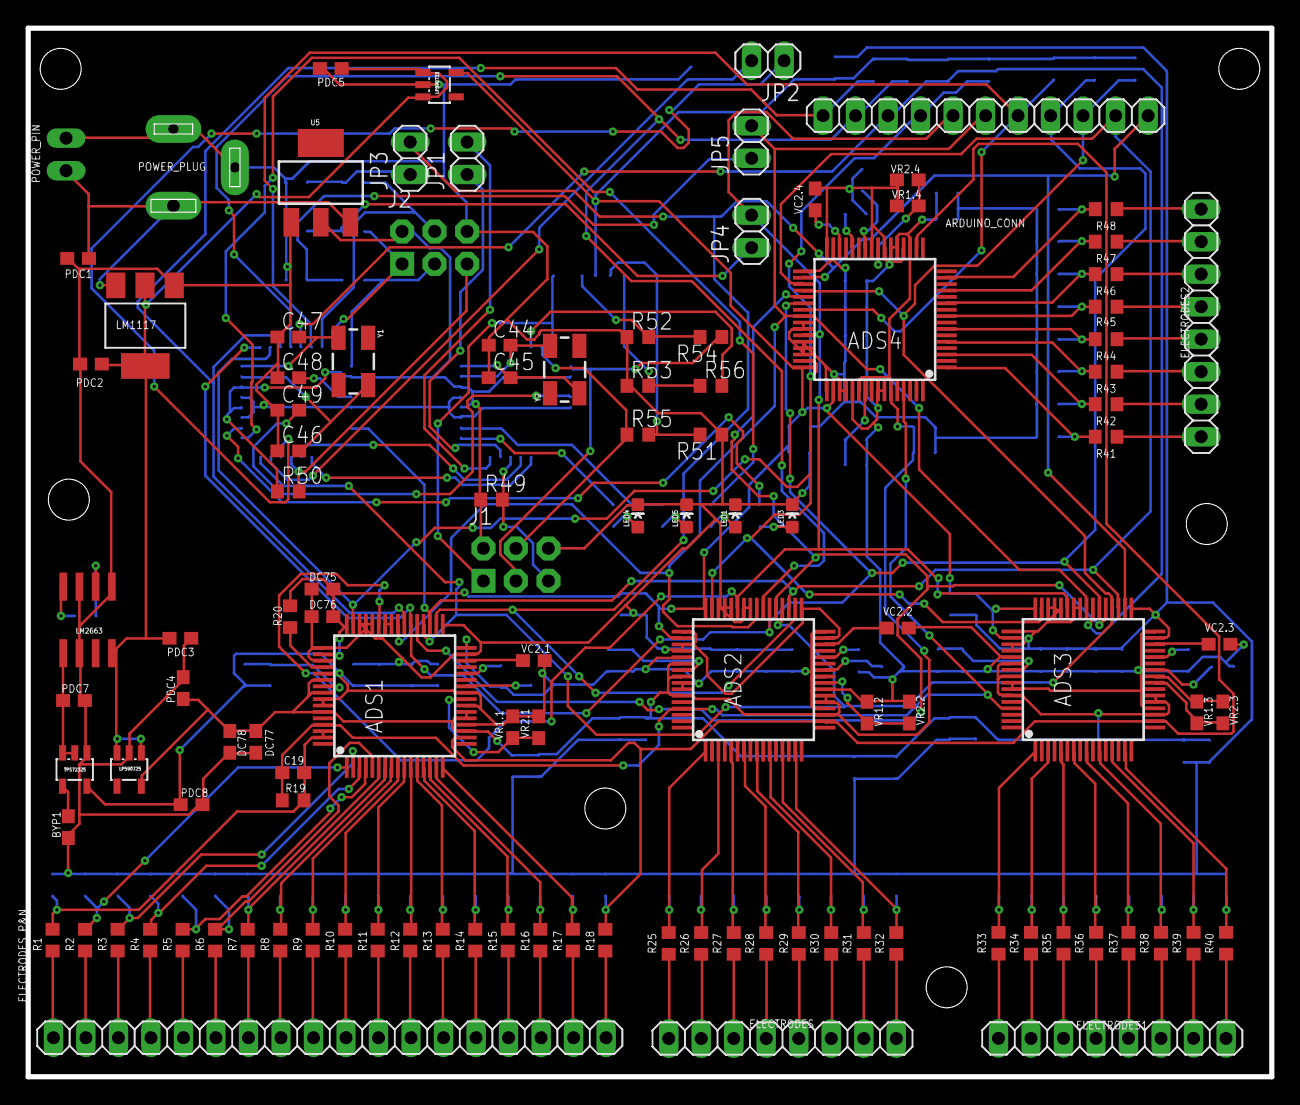
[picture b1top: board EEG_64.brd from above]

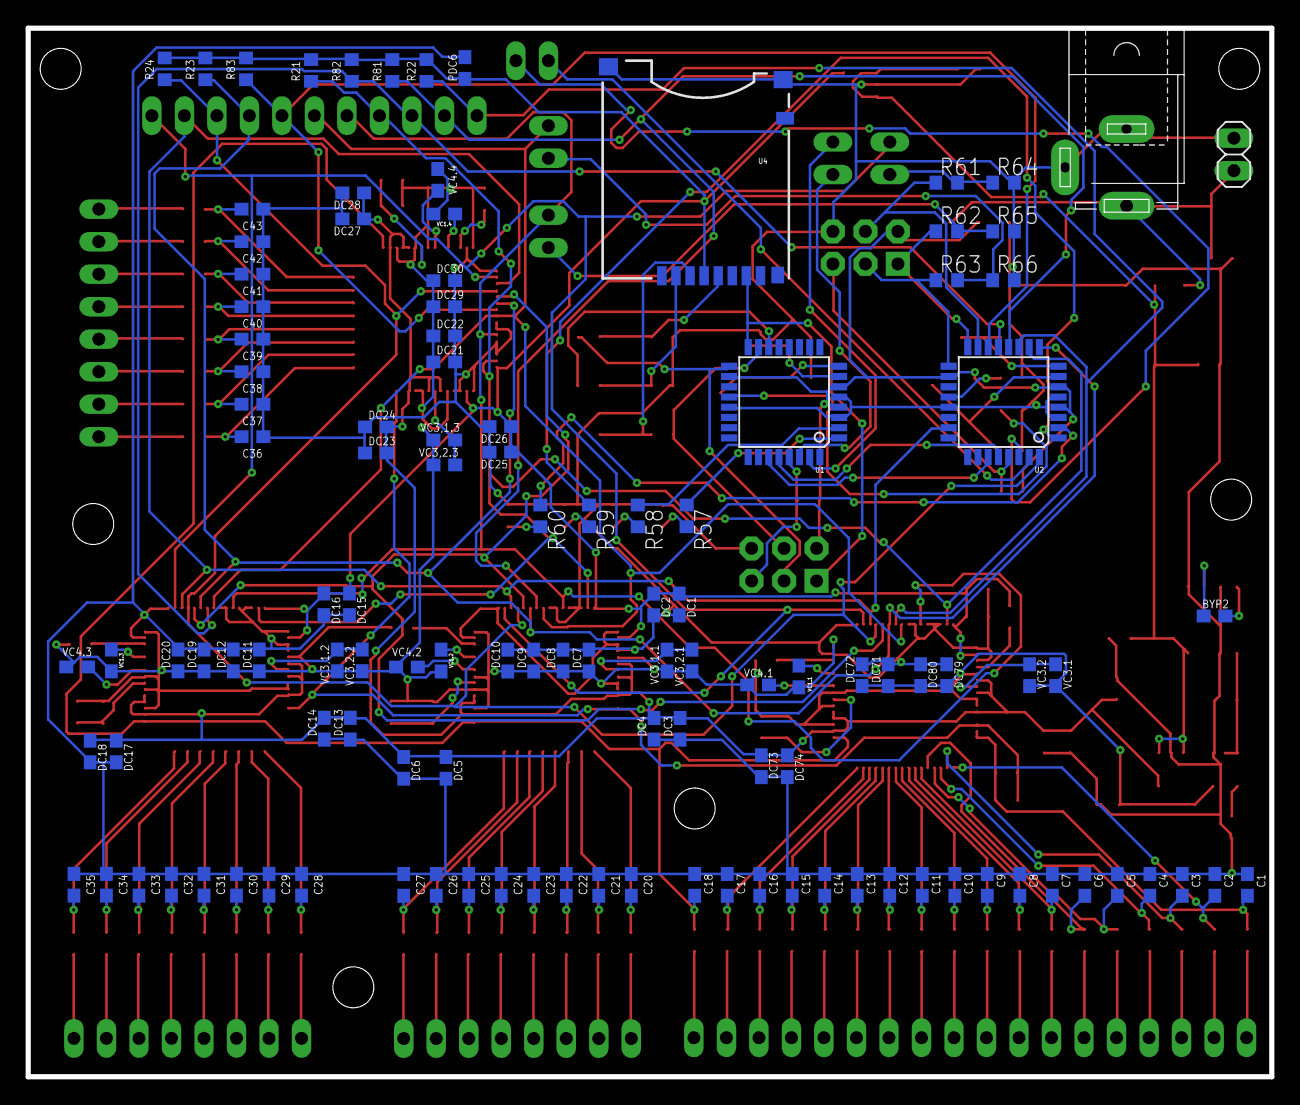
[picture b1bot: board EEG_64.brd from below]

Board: 2 copper layers, 97.2 x 81.9 mm, 229 parts (118 on the bottom side), 164 nets.

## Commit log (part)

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2018-02-01 Add files via upload
    this is a raw finished board and this needs further improvements with reverse insulation and power management.
    The next version i shall upload shall be a bit modular than this along with some battery management options, RTOs and more LEDs for indications.

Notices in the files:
README.md:
License: Apache 2.0
parts and their libraries:
SparkFun-DigitalIC: Licensing: Creative Commons ShareAlike 4.0 International - https://creativecommons.org/licenses/by-sa/4.0
